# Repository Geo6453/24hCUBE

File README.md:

# 24hCUBE
### https://24hducode.forge.apps.education.fr/
### https://docs.python.org/fr/3/library/json.html

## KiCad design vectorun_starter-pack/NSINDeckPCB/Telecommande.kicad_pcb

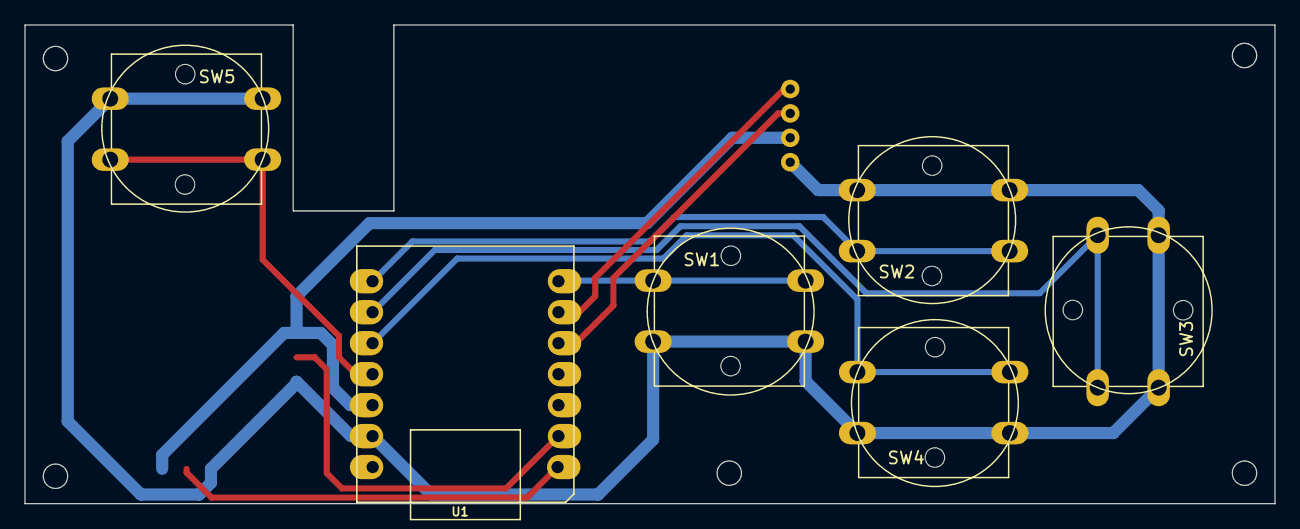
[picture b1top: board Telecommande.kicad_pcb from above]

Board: 2 copper layers, 102.5 x 39.2 mm, 7 parts (1 on the bottom side), 9 nets.

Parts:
J1: Grove_Connector; Grove_1x04
SW1, SW2, SW3, SW4, SW5: SW_Push; SW_PUSH-13mmGotronic
U1: MODULE-SEEEDUINO-XIAO-ESP32C3; MOUDLE14P-SMD-2.54-21X17.8MM

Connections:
+3.3V: J1.2 (Vcc), U1.12 (3V3)
GND: J1.1 (GND), SW1.2, SW2.2, SW3.2, SW4.2, SW5.2, U1.13 (GND)
unnamed: J1.4 (SCL), U1.6 (PA9_A5_D5_SCL)
unnamed: J1.3 (SDA), U1.5 (PA8_A4_D4_SDA)
unnamed: SW4.1, U1.10 (PA5_A9_D9_MISO)
unnamed: SW5.1, U1.11 (PA6_A10_D10_MOSI)
unnamed: SW3.1, U1.9 (PA7_A8_D8_SCK)
unnamed: SW1.1, U1.7 (PB08_A6_D6_TX)
unnamed: SW2.1, U1.8 (PB09_A7_D7_RX)
